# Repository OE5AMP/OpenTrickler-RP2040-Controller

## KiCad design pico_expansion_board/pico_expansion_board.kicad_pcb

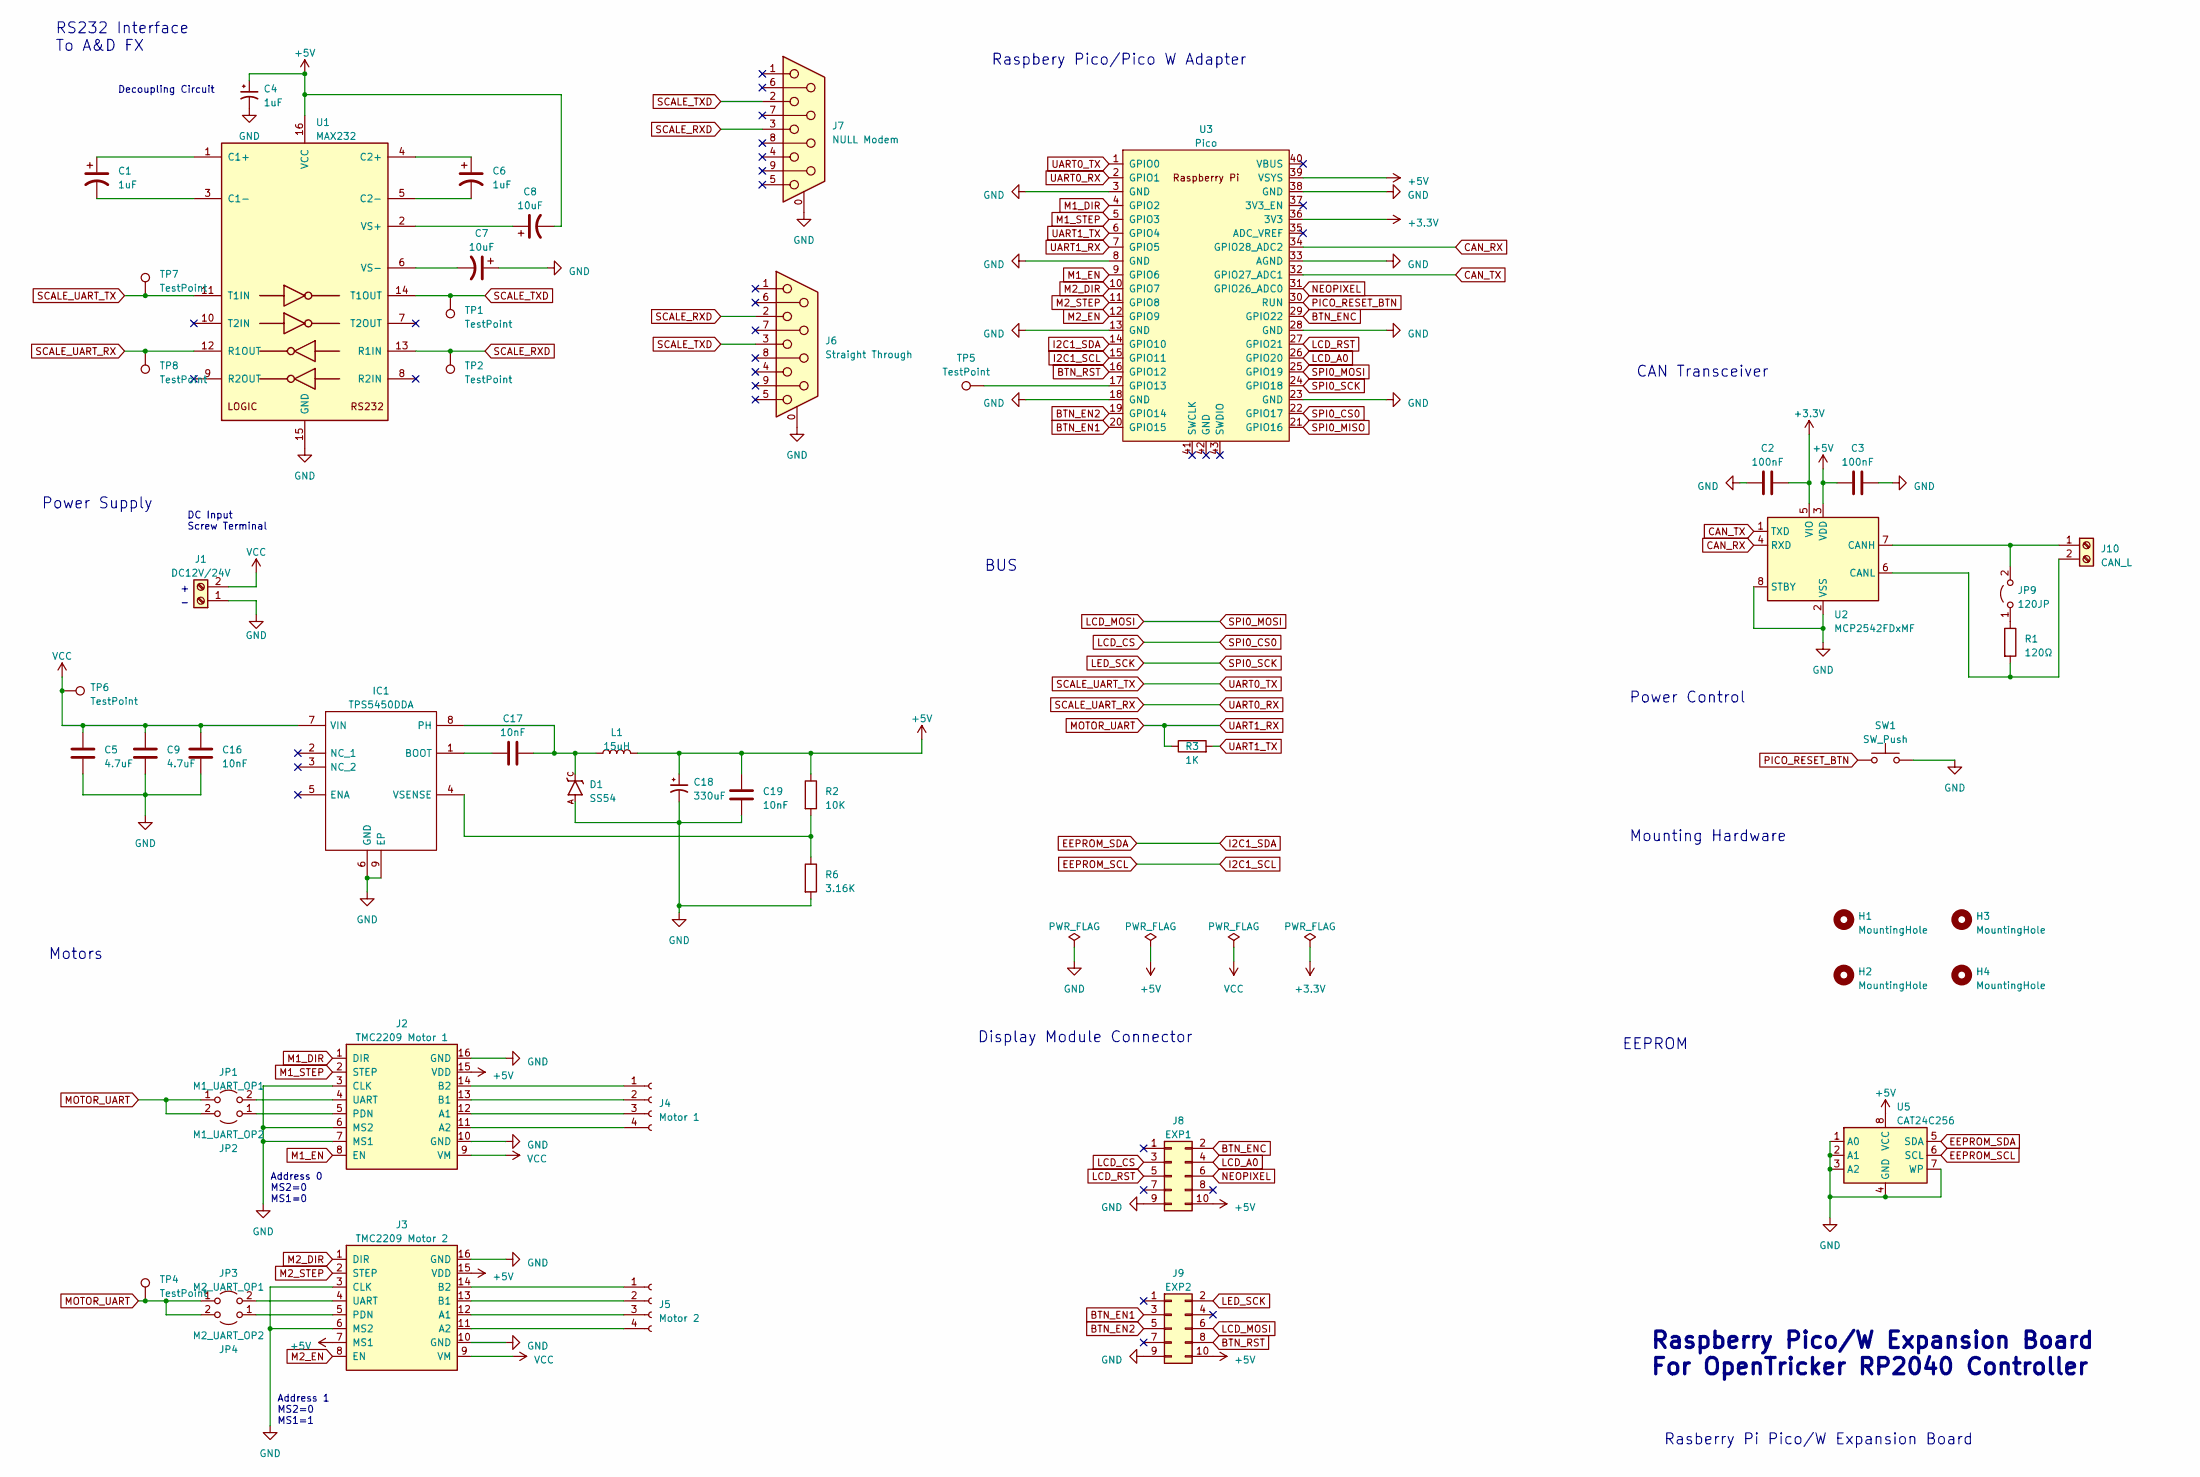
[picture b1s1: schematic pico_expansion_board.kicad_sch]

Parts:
C1, C4, C6: 1uF; C_0805_2012Metric
C2, C3: 100nF; C_0805_2012Metric
C5, C9: 4.7uF; C_0805_2012Metric
C7, C8: 10uF; C_0805_2012Metric
C16, C17, C19: 10nF; C_0805_2012Metric
C18: 330uF; CP_Elec_10x10.5
D1: SS54; DO-214AC
H1, H2, H3, H4: MountingHole; MountingHole_3.2mm_M3_Pad
IC1: TPS5450DDA; SOIC127P600X170-9N; Mouser Part Number 595-TPS5450DDA
J1: DC12V/24V; TerminalBlock_bornier-2_P5.08mm
J2: TMC2209 Motor 1; Conn_StepStick
J3: TMC2209 Motor 2; Conn_StepStick
J4: Motor 1; JST_XH_B4B-XH-AM_1x04_P2.50mm_Vertical
J5: Motor 2; JST_XH_B4B-XH-AM_1x04_P2.50mm_Vertical
J6: Straight Through; DSUB-9_Male_Horizontal_P2.77x2.84mm_EdgePinOffset7.70mm_Hou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
J7: NULL Modem; DSUB-9_Male_Horizontal_P2.77x2.84mm_EdgePinOffset7.70mm_Hou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
J8: EXP1; IDC-Header_2x05_P2.54mm_Vertical
J9: EXP2; IDC-Header_2x05_P2.54mm_Vertical
J10: CAN_L; TerminalBlock_bornier-2_P5.08mm
JP1: M1_UART_OP1; PinHeader_1x02_P2.00mm_Vertical
JP2: M1_UART_OP2; PinHeader_1x02_P2.00mm_Vertical
JP3: M2_UART_OP1; PinSocket_1x02_P2.00mm_Vertical
JP4: M2_UART_OP2; PinSocket_1x02_P2.00mm_Vertical
JP9: 120JP; PinHeader_1x02_P2.00mm_Vertical
L1: 15uH; Power Inductor 10x11
R1: 120Ω; R_0805_2012Metric
R2: 10K; R_0805_2012Metric
R3: 1K; R_0805_2012Metric
R6: 3.16K; R_0805_2012Metric
SW1: SW_Push; SW_Push_1P1T_NO_6x6mm_H9.5mm
TP1, TP2, TP4, TP5, TP6, TP7, TP8: TestPoint; TestPoint_Pad_2.0x2.0mm
U1: MAX232; SOIC-16_3.9x9.9mm_P1.27mm
U2: MCP2542FDxMF; SO-8_3.9x4.9mm_P1.27mm
U3: Pico; RPi_Pico_SMD_TH
U5: CAT24C256; SO-8_3.9x4.9mm_P1.27mm

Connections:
+3.3V: C2.2, U2.5 (VIO), U3.36 (3V3)
+5V: C3.1, C4.1, C8.2, C18.1, C19.1, J2.15 (VDD), J3.7 (MS1), J3.15 (VDD), J8.10, J9.10, L1.2, R2.1, U1.16 (VCC), U2.3 (VDD), U3.39 (VSYS), U5.8 (VCC)
BTN_EN1: J9.3, U3.20 (GPIO15)
BTN_EN2: J9.5, U3.19 (GPIO14)
BTN_ENC: J8.2, U3.29 (GPIO22)
BTN_RST: J9.8, U3.16 (GPIO12)
CAN_RX: U2.4 (RXD), U3.34 (GPIO28_ADC2)
CAN_TX: U2.1 (TXD), U3.32 (GPIO27_ADC1)
EEPROM_SCL: U3.15 (GPIO11), U5.6 (SCL)
EEPROM_SDA: U3.14 (GPIO10), U5.5 (SDA)
GND: C2.1, C3.2, C4.2, C5.2, C7.1, C9.2, C16.2, C18.2, C19.2, D1.A, IC1.6 (GND), IC1.9 (EP), J1.1, J2.3 (CLK), J2.6 (MS2), J2.7 (MS1), J2.10 (GND), J2.16 (GND), J3.3 (CLK), J3.6 (MS2), J3.10 (GND), J3.16 (GND), J6.0 (PAD), J7.0 (PAD), J8.9, J9.9, R6.2, SW1.2, U1.15 (GND), U2.2 (VSS), U2.8 (STBY), U3.3 (GND), U3.8 (GND), U3.13 (GND), U3.18 (GND), U3.23 (GND), U3.28 (GND), U3.33 (AGND), U3.38 (GND), U5.1 (A0), U5.2 (A1), U5.3 (A2), U5.4 (GND), U5.7 (WP); also elsewhere on the board
LCD_A0: J8.4, U3.26 (GPIO20)
LCD_CS: J8.3, U3.22 (GPIO17)
LCD_MOSI: J9.6, U3.25 (GPIO19)
LCD_RST: J8.5, U3.27 (GPIO21)
LED_SCK: J9.2, U3.24 (GPIO18)
M1_DIR: J2.1 (DIR), U3.4 (GPIO2)
M1_EN: J2.8 (EN), U3.9 (GPIO6)
M1_STEP: J2.2 (STEP), U3.5 (GPIO3)
M2_DIR: J3.1 (DIR), U3.10 (GPIO7)
M2_EN: J3.8 (EN), U3.12 (GPIO9)
M2_STEP: J3.2 (STEP), U3.11 (GPIO8)
MOTOR_UART: JP1.1 (A), JP2.2 (B), JP3.1 (A), JP4.2 (B), R3.1, TP4.1, U3.7 (GPIO5)
NEOPIXEL: J8.6, U3.31 (GPIO26_ADC0)
unnamed: C17.1, IC1.1 (BOOT)
unnamed: C17.2, D1.C, IC1.8 (PH), L1.1
unnamed: IC1.4 (VSENSE), R2.2, R6.1
unnamed: J2.12 (A1), J4.3
unnamed: J2.11 (A2), J4.4
unnamed: J2.13 (B1), J4.2
unnamed: J2.14 (B2), J4.1
unnamed: J2.4 (PDN), JP1.2 (B)
unnamed: J2.5 (UART), JP2.1 (A)
unnamed: J3.12 (A1), J5.3
unnamed: J3.11 (A2), J5.4
unnamed: J3.13 (B1), J5.2
unnamed: J3.14 (B2), J5.1
unnamed: J3.4 (PDN), JP3.2 (B)
unnamed: J3.5 (UART), JP4.1 (A)
unnamed: J10.1, JP9.2 (B), U2.7 (CANH)
unnamed: J10.2, R1.2, U2.6 (CANL)
unnamed: JP9.1 (A), R1.1
unnamed: C1.1, U1.1 (C1+)
unnamed: C1.2, U1.3 (C1-)
unnamed: C6.1, U1.4 (C2+)
unnamed: C6.2, U1.5 (C2-)
unnamed: C8.1, U1.2 (VS+)
unnamed: C7.2, U1.6 (VS-)
unnamed: TP5.1, U3.17 (GPIO13)
PICO_RESET_BTN: SW1.1, U3.30 (RUN)
SCALE_RXD: J6.2, J7.3, TP2.1, U1.13 (R1IN)
SCALE_TXD: J6.3, J7.2, TP1.1, U1.14 (T1OUT)
SCALE_UART_RX: TP8.1, U1.12 (R1OUT), U3.2 (GPIO1)
SCALE_UART_TX: TP7.1, U1.11 (T1IN), U3.1 (GPIO0)
SPI0_MISO: U3.21 (GPIO16)
UART1_TX: R3.2, U3.6 (GPIO4)
VCC: C5.1, C9.1, C16.1, IC1.7 (VIN), J1.2, J2.9 (VM), J3.9 (VM), TP6.1; also elsewhere on the board

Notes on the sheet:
Motors
Address 1 MS2=0 MS1=1
BUS
Mounting Hardware
EEPROM
Display Module Connector
Raspberry Pico/W Expansion Board For OpenTricker RP2040 Controller
Decoupling Circuit
DC Input Screw Terminal
RS232 Interface To A&D FX
Power Supply
Rasberry Pi Pico/W Expansion Board
Power Control
CAN Transceiver
Raspbery Pico/Pico W Adapter
Address 0 MS2=0 MS1=0

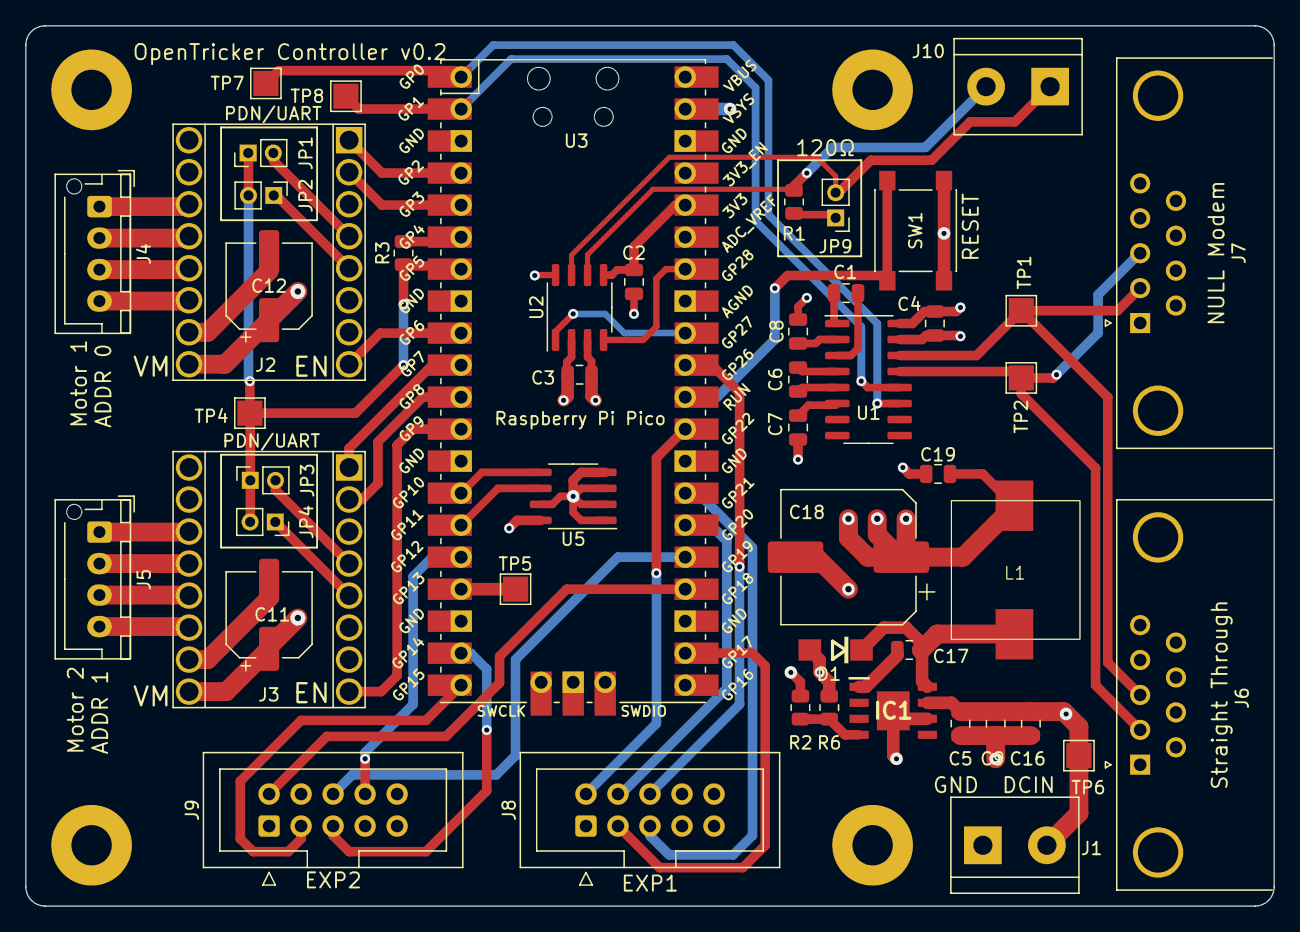
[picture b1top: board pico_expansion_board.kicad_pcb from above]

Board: 4 copper layers, 99.1 x 69.8 mm, 53 parts (0 on the bottom side), 56 nets.

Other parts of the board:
C11, C12: 100uF; CP_Elec_6.3x7.7

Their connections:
GND: C11.2, C12.2; also elsewhere on the board
VCC: C11.1, C12.1; also elsewhere on the board

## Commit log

2023-02-23 Initial commit of pcb design
2023-02-23 Re-arrange component location
2023-02-23 Add external eeprom
2023-02-26 Update PCB and schematic design
2023-03-02 Update design
2023-03-02 add production file
2023-03-02 Add 3d models for pico and stepper drivers
2023-03-02 Add export model
2023-03-03 Update production file, update STEP models
2023-03-05 Update to v0.2, include additional caps for StepStick driver VM input
2023-03-06 Add new BOM
2023-03-06 Minor adjustment to the VCC plane
2023-03-06 Create BOM file
